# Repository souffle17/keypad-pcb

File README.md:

# keypad-pcb      

A simple 2x3 mechanical keypad.       

Case parts are designed for CNC machining, stacked and screwed together. Firmware uses QMK.       

### Resources:
- https://guide.zykrah.me/
- https://www.masterzen.fr/2020/05/03/designing-a-keyboard-part-1/
- https://wiki.ai03.com/books/pcb-design/chapter/pcb-designer-guide

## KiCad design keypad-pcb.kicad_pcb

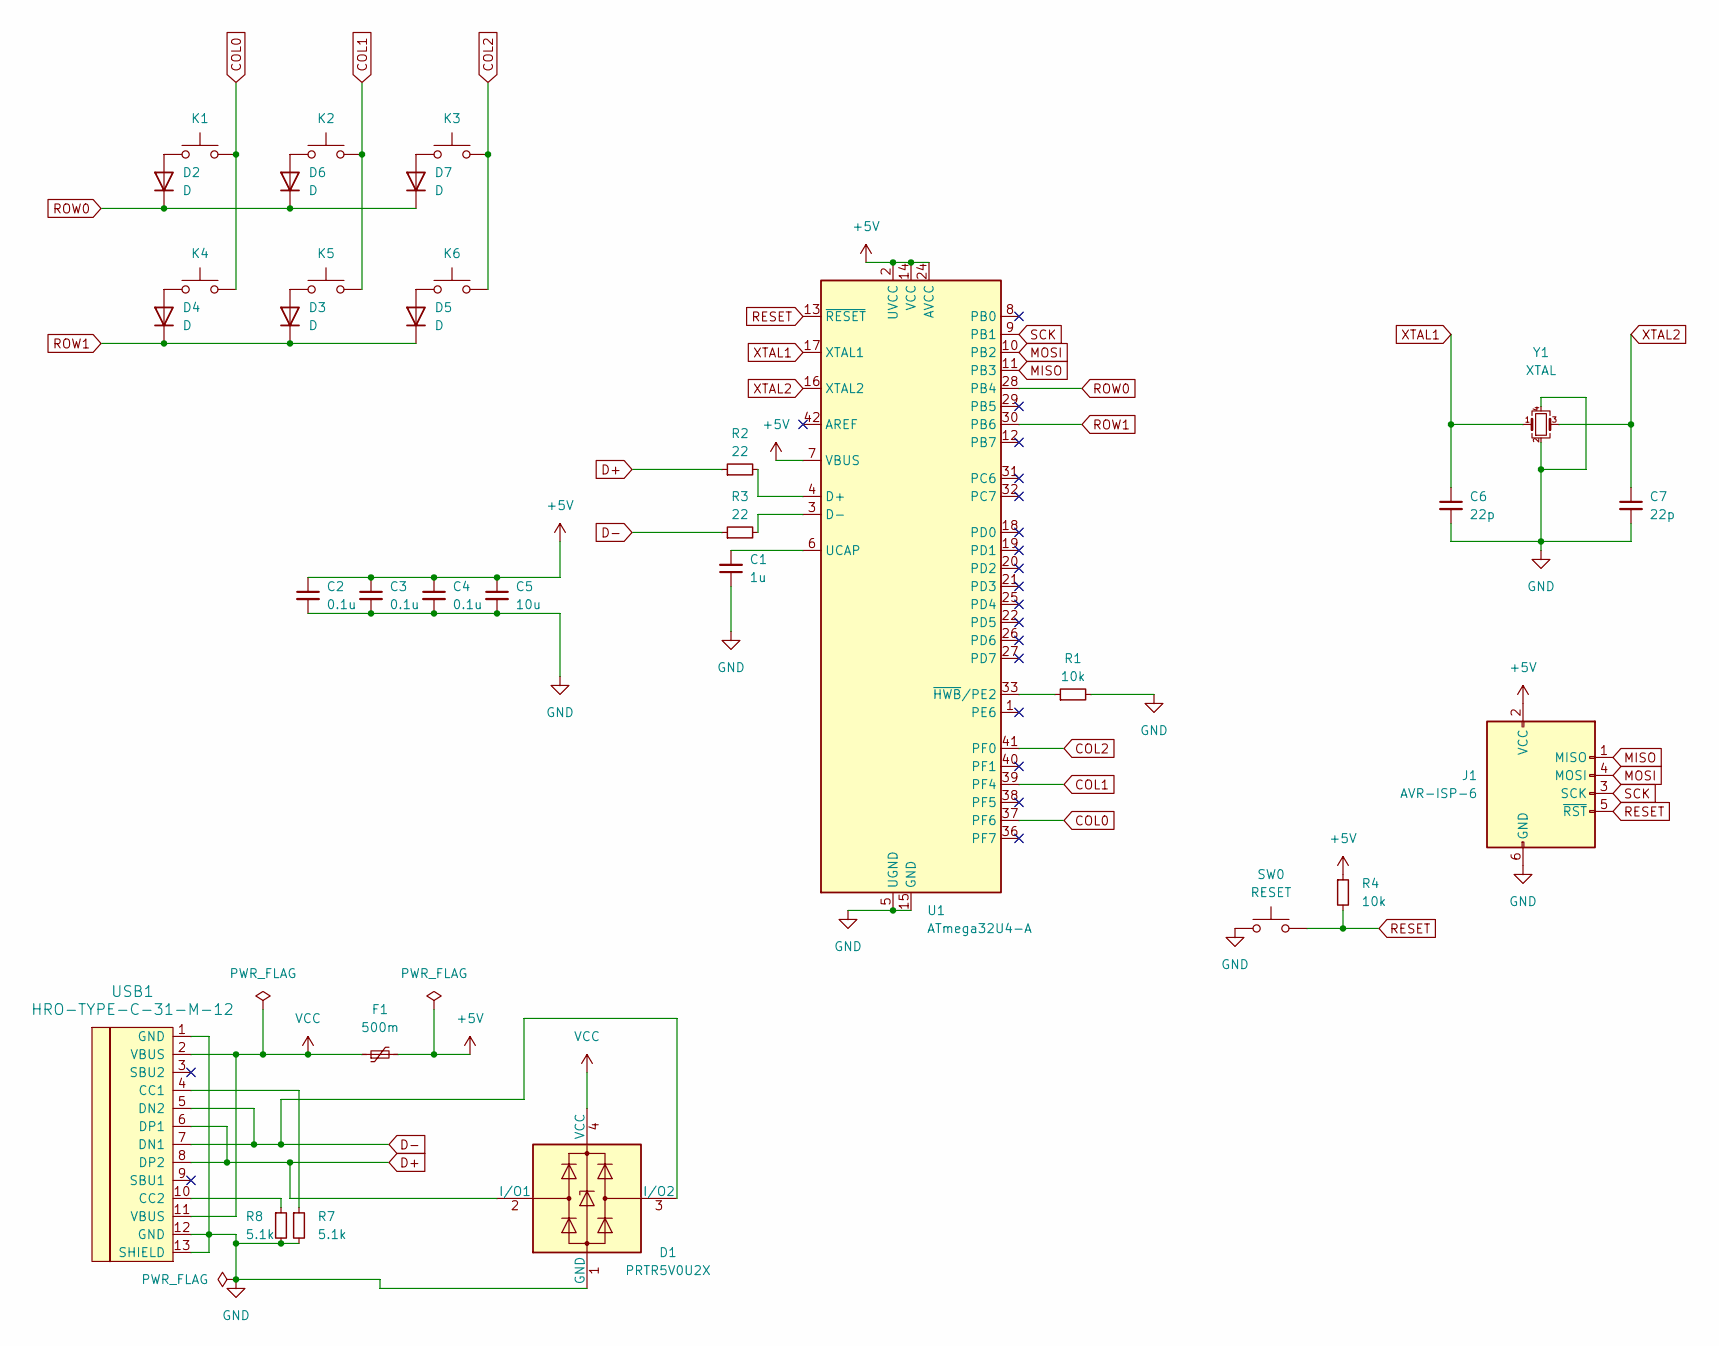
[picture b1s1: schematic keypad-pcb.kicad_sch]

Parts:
C1: 1u; C_0805_2012Metric
C2, C3, C4: 0.1u; C_0805_2012Metric
C5: 10u; C_0805_2012Metric
C6, C7: 22p; C_0805_2012Metric
D1: PRTR5V0U2X; SOT143B
D2, D3, D4, D5, D6, D7: D; D_SOD-123
F1: 500m; Fuse_1206_3216Metric
J1: AVR-ISP-6; Reset_Pretty-Mask
K1, K2, K3, K4, K5, K6: SW_Push; SW_MX_HS_1u
R1, R4: 10k; R_0805_2012Metric
R2, R3: 22; R_0805_2012Metric
R7, R8: 5.1k; R_0805_2012Metric
SW0: RESET; SW_SPST_SKQG_WithStem
U1: ATmega32U4-A; TQFP-44_10x10mm_P0.8mm
USB1: HRO-TYPE-C-31-M-12
Y1: XTAL; Crystal_SMD_3225-4Pin_3.2x2.5mm

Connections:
+5V: C2.1, C3.1, C4.1, C5.1, F1.2, J1.2 (VCC), R4.1, U1.2 (UVCC), U1.7 (VBUS), U1.14 (VCC), U1.24 (AVCC), U1.34 (VCC), U1.44 (AVCC)
COL0: K1.2, K4.2, U1.37 (PF6)
COL1: K2.2, K5.2, U1.39 (PF4)
COL2: K3.2, K6.2, U1.41 (PF0)
D+: D1.2 (I/O1), R2.1, USB1.6 (DP1), USB1.8 (DP2)
D-: D1.3 (I/O2), R3.1, USB1.5 (DN2), USB1.7 (DN1)
GND: C1.1, C2.2, C3.2, C4.2, C5.2, C6.2, C7.2, D1.1 (GND), J1.6 (GND), R1.2, R7.2, R8.2, SW0.1, U1.5 (UGND), U1.15 (GND), U1.23 (GND), U1.35 (GND), U1.43 (GND), USB1.1 (GND), USB1.12 (GND), USB1.13 (SHIELD), Y1.2, Y1.4
MISO: J1.1 (MISO), U1.11 (PB3)
MOSI: J1.4 (MOSI), U1.10 (PB2)
unnamed: D2.2 (A), K1.1
unnamed: D3.2 (A), K5.1
unnamed: D4.2 (A), K4.1
unnamed: D5.2 (A), K6.1
unnamed: D6.2 (A), K2.1
unnamed: D7.2 (A), K3.1
unnamed: R2.2, U1.4 (D+)
unnamed: R3.2, U1.3 (D-)
unnamed: C1.2, U1.6 (UCAP)
unnamed: R1.1, U1.33 (~HWB/PE2)
unnamed: R7.1, USB1.4 (CC1)
unnamed: R8.1, USB1.10 (CC2)
RESET: J1.5 (~RST), R4.2, SW0.2, U1.13 (~RESET)
ROW0: D2.1 (K), D6.1 (K), D7.1 (K), U1.28 (PB4)
ROW1: D3.1 (K), D4.1 (K), D5.1 (K), U1.30 (PB6)
SCK: J1.3 (SCK), U1.9 (PB1)
VCC: D1.4 (VCC), F1.1, USB1.2 (VBUS), USB1.11 (VBUS)
XTAL1: C6.1, U1.17 (XTAL1), Y1.1
XTAL2: C7.1, U1.16 (XTAL2), Y1.3

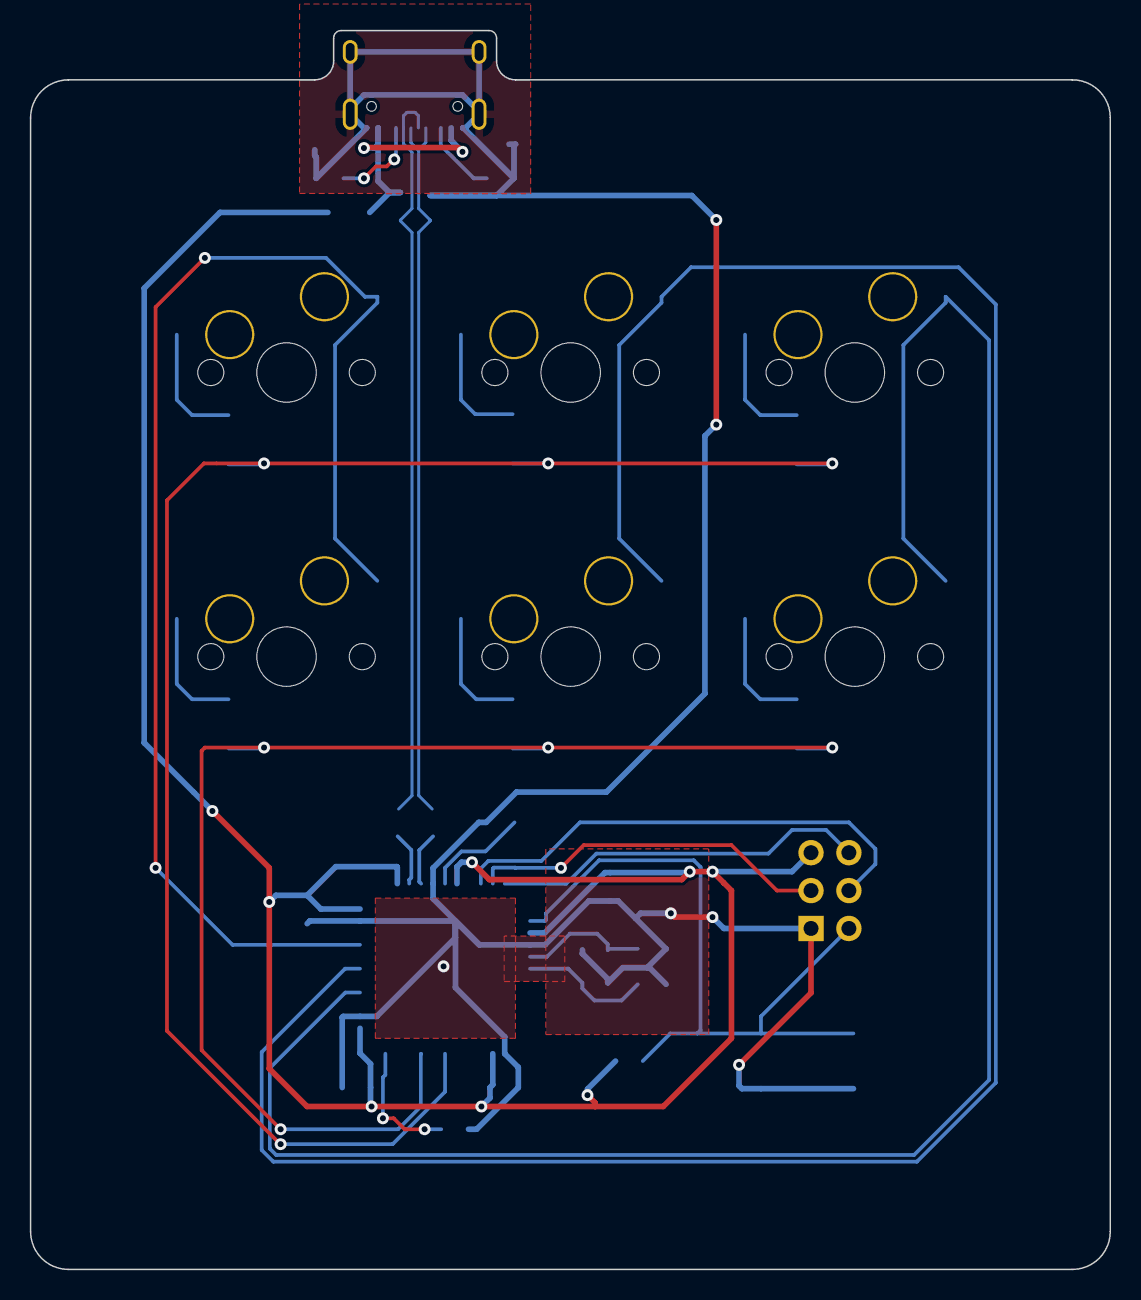
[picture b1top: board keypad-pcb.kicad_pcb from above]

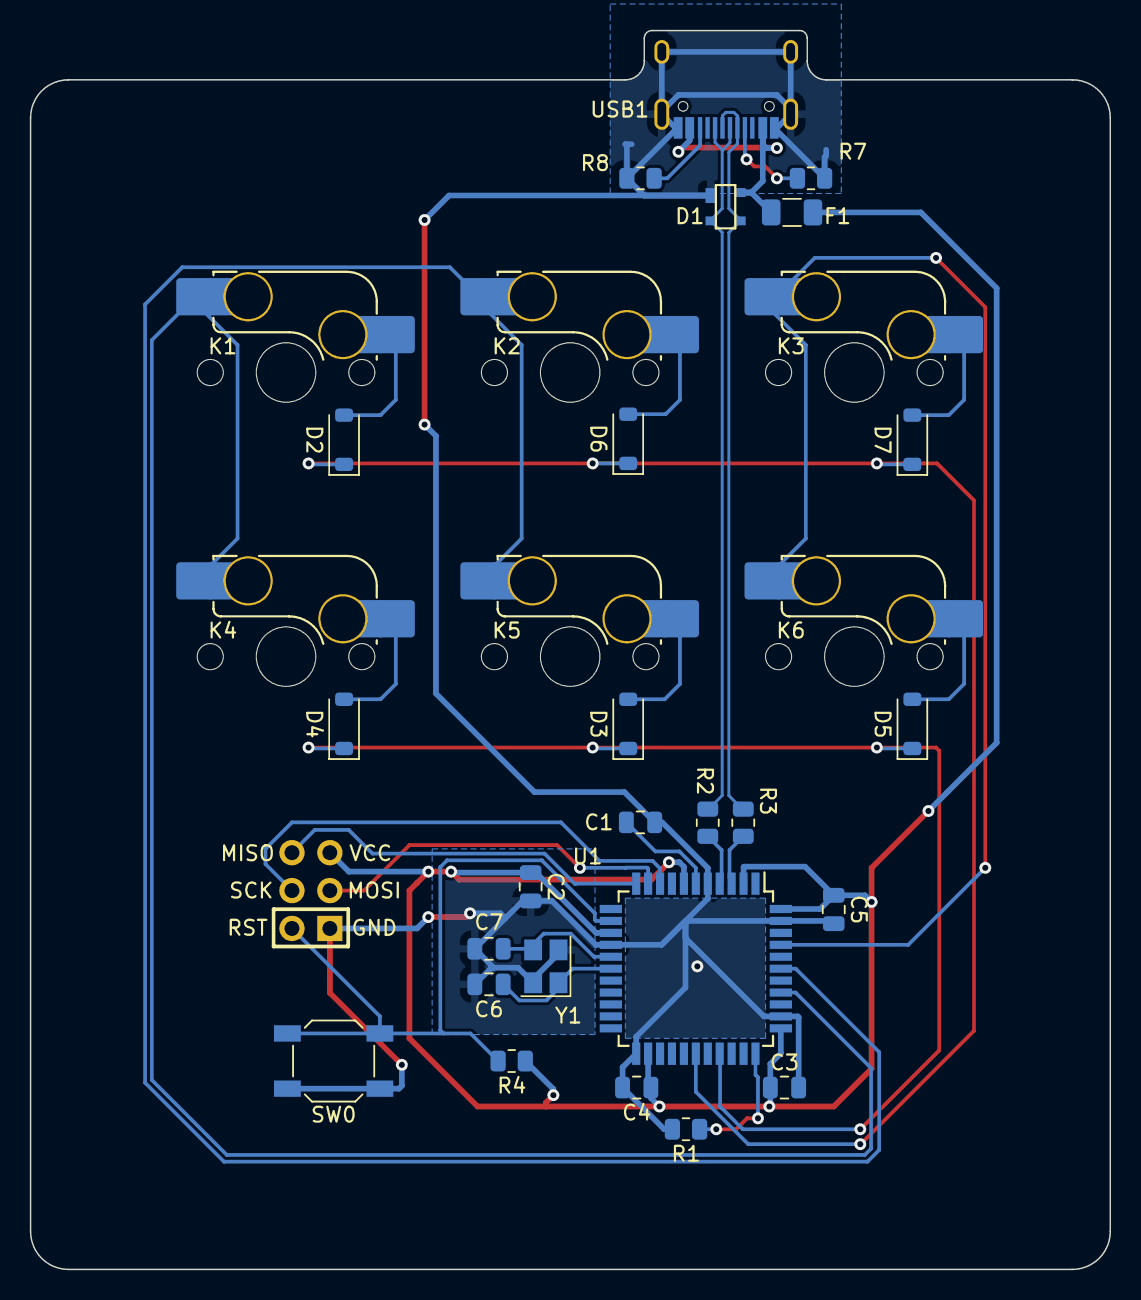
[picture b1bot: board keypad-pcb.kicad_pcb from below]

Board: 2 copper layers, 72.4 x 83.1 mm, 32 parts (32 on the bottom side), 28 nets.

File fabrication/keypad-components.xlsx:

Comment | Designator | Footprint | JLCPCB Part #（optional）
D | D5,D2,D6,D4,D3,D7 | SOD-123 | C77978
5.1k | R7,R8 | 0805 | C84375
ATmega32U4-A | U1 | TQFP-44 | C44854
RESET | SW0 | SKQG | C115351
10k | R4,R1 | 0805 | C84376
HRO-TYPE-C-31-M-12 | USB1 | HRO-TYPE-C-31-M-12 | C165948
0.1u | C2,C3,C4 | 0805 | C1711
1u | C1 | 0805 | C116352
22p | C6,C7 | 0805 | C1804
22 | R2,R3 | 0805 | C844832
PRTR5V0U2X | D1 | SOT143B | C12333
10u | C5 | 0805 | C95841
500m | F1 | 1206 | C70069
XTAL | Y1 | 3225 | C255909

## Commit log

2023-12-25 Update LICENSE
2023-12-25 project files
2023-12-25 update gitignore
2023-12-25 add libraries
2023-12-25 add modules, mcu, usb, debounce, reset, and clock
2023-12-25 esd protection
2023-12-25 matrix
2023-12-25 mcu wiring
2023-12-25 power flag
2023-12-25 readme
2023-12-25 module
2023-12-25 modules
2023-12-25 footprints
2023-12-25 pcb start
2023-12-25 arrange parts
2023-12-25 some routing
2023-12-26 clock+more
2023-12-26 complete routing
2023-12-26 edge cut
2023-12-26 smoothed corners
2023-12-26 finish fills
2023-12-26 missing ground
2023-12-26 formatting
2023-12-29 manufacturing files
2023-12-29 case
2023-12-30 firmware
2024-01-03 additional keymaps
